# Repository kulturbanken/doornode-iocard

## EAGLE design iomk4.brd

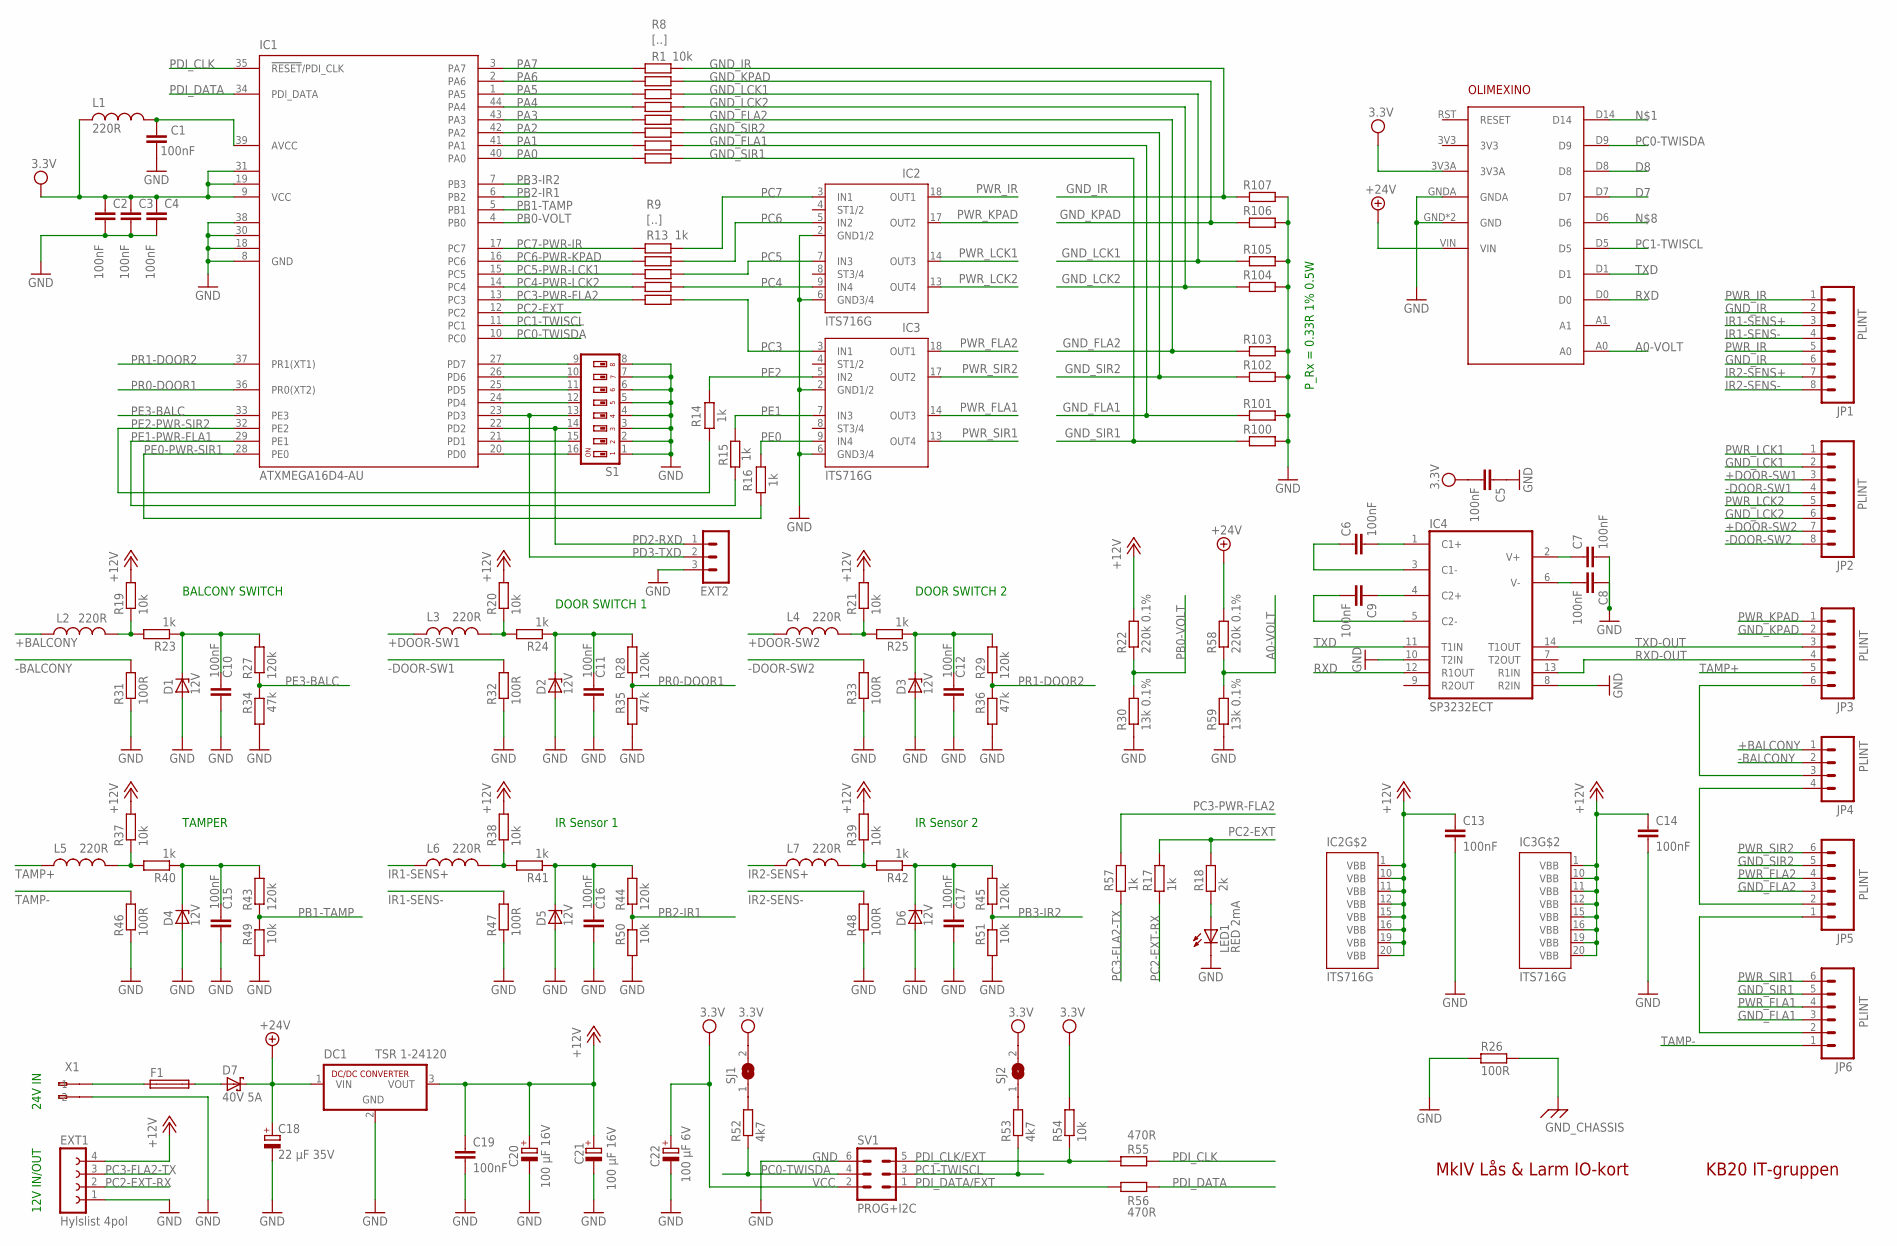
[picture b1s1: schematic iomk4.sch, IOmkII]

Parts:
C1, C2, C3, C4, C5, C6, C7, C8, C9, C10, C11, C12, C13, C14, C15, C16, C17, C19: 100nF; C0805
C18: 22 µF 35V; D/7343-31R
C20, C21: 100 µF 16V; D/7343-31R
C22: 100 µF 6V; CT6032
D1, D2, D3, D4, D5, D6: 12V; SOD80C
D7: 40V 5A; SMB
DC1: TSR 1-24120; SIP3
EXT1: Hylslist 4pol; FE04
EXT2: DEBUG PINS; MA03
F1: Fuse Holder; FTP/60
IC1: ATXMEGA16D4-AU; TQFP44; MPN ATXMEGA16A4-AU
IC2, IC3: ITS716G; PG-DSO-20
IC4: SP3232ECT; SO16L; MPN MAX3232CSE+
JP1, JP2: PLINT; FK-MPT-8-3,5
JP3, JP5, JP6: PLINT; FK-MPT-6-3,5
JP4: PLINT; FK-MPT-4-3.5
L1, L2, L3, L4, L5, L6, L7: 220R; L0805
LED1: RED 2mA; SML0603
OLIMEXINO-STM1: OLIMEXINO; OLIMEXINO-STM32
R1, R2, R3, R4, R5, R6, R7, R8, R19, R20, R21, R37, R38, R39, R49, R50, R51, R54: 10k; R0805
R9, R10, R11, R12, R13, R14, R15, R16, R17, R23, R24, R25, R40, R41, R42, R57: 1k; R0805
R18: 2k; R0805
R22, R58: 220k 0.1%; R0805
R26, R31, R32, R33, R46, R47, R48: 100R; R0805
R27, R28, R29, R43, R44, R45: 120k; R0805
R30, R59: 13k 0.1%; R0805
R34, R35, R36: 47k; R0805
R52, R53: 4k7; R0805
R55, R56: 470R; R0805
R100, R101, R102, R103, R104, R105, R106, R107: 0.33R; R1210
S1: DIP switches; DIL08-SMD-MINI
SJ1, SJ2: Solder jumper; SJ
SV1: PROG+I2C; ML6L
X1: PLINT; 255-402-5

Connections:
+12V: C13.1, C14.1, C19.1, C20.+, C21.+, DC1.3 (VOUT), EXT1.4, IC2.1 (VBB), IC2.10 (VBB), IC2.11 (VBB), IC2.12 (VBB), IC2.15 (VBB), IC2.16 (VBB), IC2.19 (VBB), IC2.20 (VBB), IC3.1 (VBB), IC3.10 (VBB), IC3.11 (VBB), IC3.12 (VBB), IC3.15 (VBB), IC3.16 (VBB), IC3.19 (VBB), IC3.20 (VBB), R19.2, R20.2, R21.2, R22.2, R37.2, R38.2, R39.2
+24V: C18.+, D7.C, DC1.1 (VIN), OLIMEXINO-STM1.VIN, R58.2
+BALCONY: JP4.1, L2.1
+DOOR-SW1: JP2.3, L3.1
+DOOR-SW2: JP2.7, L4.1
-BALCONY: JP4.2, R31.2
-DOOR-SW1: JP2.4, R32.2
-DOOR-SW2: JP2.8, R33.2
A0-VOLT: OLIMEXINO-STM1.A0, R58.1, R59.2
D7: OLIMEXINO-STM1.D7
D8: OLIMEXINO-STM1.D8
GND: C1.2, C2.2, C3.2, C4.2, C5.1, C7.2, C8.1, C10.2, C11.2, C12.2, C13.2, C14.2, C15.2, C16.2, C17.2, C18.-, C19.2, C20.-, C21.-, C22.-, D1.A, D2.A, D3.A, D4.A, D5.A, D6.A, DC1.2 (GND), EXT1.1, EXT2.3, IC1.8 (GND), IC1.18 (GND1), IC1.30 (GND2), IC1.38 (GND3), IC2.2 (GND1/2), IC2.6 (GND3/4), IC3.2 (GND1/2), IC3.6 (GND3/4), IC4.8 (R2IN), IC4.10 (T2IN), IC4.15 (GND), LED1.C, OLIMEXINO-STM1.GND, OLIMEXINO-STM1.GND2 (GND), OLIMEXINO-STM1.GNDA, R26.2, R30.1, R31.1, R32.1, R33.1, R34.2, R35.2, R36.2, R46.1, R47.1, R48.1, R49.2, R50.2, R51.2, R59.1, R100.2, R101.2, R102.2, R103.2, R104.2, R105.2, R106.2, R107.2, S1.1, S1.2, S1.3, S1.4, S1.5, S1.6, S1.7, S1.8, SV1.6, X1.A2 (-2)
GND_CHASSIS: R26.1
GND_FLA1: JP6.3, R2.2, R101.1
GND_FLA2: JP5.3, R4.2, R103.1
GND_IR: JP1.2, JP1.6, R8.2, R107.1
GND_KPAD: JP3.2, R7.2, R106.1
GND_LCK1: JP2.2, R6.2, R105.1
GND_LCK2: JP2.6, R5.2, R104.1
GND_SIR1: JP6.5, R1.2, R100.1
GND_SIR2: JP5.5, R3.2, R102.1
IR1-SENS+: JP1.3, L6.1
IR1-SENS-: JP1.4, R47.2
IR2-SENS+: JP1.7, L7.1
IR2-SENS-: JP1.8, R48.2
unnamed: D7.A, F1.2
unnamed: C1.1, IC1.39 (AVCC), L1.2
unnamed: R53.2, SJ2.1
unnamed: LED1.A, R18.2
unnamed: L3.2, R20.1, R24.2
unnamed: L2.2, R19.1, R23.2
unnamed: C10.1, D1.C, R23.1, R27.2
unnamed: C11.1, D2.C, R24.1, R28.2
unnamed: L4.2, R21.1, R25.2
unnamed: F1.1, X1.A1 (-1)
unnamed: C12.1, D3.C, R25.1, R29.2
unnamed: R52.2, SJ1.1
unnamed: L6.2, R38.1, R41.2
unnamed: JP3.6, JP4.3
unnamed: JP5.1, JP6.2
unnamed: L5.2, R37.1, R40.2
unnamed: JP4.4, JP5.2
unnamed: C15.1, D4.C, R40.1, R43.2
unnamed: C16.1, D5.C, R41.1, R44.2
unnamed: C7.1, IC4.2 (V+)
unnamed: C8.2, IC4.6 (V-)
unnamed: L7.2, R39.1, R42.2
unnamed: C17.1, D6.C, R42.1, R45.2
unnamed: C6.2, IC4.1 (C1+)
unnamed: C9.2, IC4.5 (C2-)
unnamed: C9.1, IC4.4 (C2+)
unnamed: C6.1, IC4.3 (C1-)
PA0: IC1.40 (PA0), R1.1
PA1: IC1.41 (PA1), R2.1
PA2: IC1.42 (PA2), R3.1
PA3: IC1.43 (PA3), R4.1
PA4: IC1.44 (PA4), R5.1
PA5: IC1.1 (PA5), R6.1
PA6: IC1.2 (PA6), R7.1
PA7: IC1.3 (PA7), R8.1
PB0-VOLT: IC1.4 (PB0), R22.1, R30.2
PB1-TAMP: IC1.5 (PB1), R43.1, R49.1
PB2-IR1: IC1.6 (PB2), R44.1, R50.1
PB3-IR2: IC1.7 (PB3), R45.1, R51.1
PC0-TWISDA: IC1.10 (PC0), OLIMEXINO-STM1.D9, R52.1, SV1.4
PC1-TWISCL: IC1.11 (PC1), OLIMEXINO-STM1.D5, R53.1, SV1.3
PC2-EXT: IC1.12 (PC2), R17.1, R18.1
PC2-EXT-RX: EXT1.2, R17.2
PC3: IC3.3 (IN1), R13.1
PC3-FLA2-TX: EXT1.3, R57.1
PC3-PWR-FLA2: IC1.13 (PC3), R13.2, R57.2
PC4: IC2.9 (IN4), R12.1
PC4-PWR-LCK2: IC1.14 (PC4), R12.2
PC5: IC2.7 (IN3), R11.1
PC5-PWR-LCK1: IC1.15 (PC5), R11.2
PC6: IC2.5 (IN2), R10.1
PC6-PWR-KPAD: IC1.16 (PC6), R10.2
PC7: IC2.3 (IN1), R9.1
PC7-PWR-IR: IC1.17 (PC7), R9.2
PD0: IC1.20 (PD0), S1.16
PD1: IC1.21 (PD1), S1.15
PD2-RXD: EXT2.1, IC1.22 (PD2), S1.14
PD3-TXD: EXT2.2, IC1.23 (PD3), S1.13
PD4: IC1.24 (PD4), S1.12
PD5: IC1.25 (PD5), S1.11
PD6: IC1.26 (PD6), S1.10
PD7: IC1.27 (PD7), S1.9
PDI_CLK: IC1.35 (!RESET!/PDI_CLK), R55.1
PDI_CLK/EXT: R54.1, R55.2, SV1.5
PDI_DATA: IC1.34 (PDI_DATA), R56.1
PDI_DATA/EXT: R56.2, SV1.1
PE0: IC3.9 (IN4), R16.1
PE0-PWR-SIR1: IC1.28 (PE0), R16.2
PE1: IC3.7 (IN3), R15.1
PE1-PWR-FLA1: IC1.29 (PE1), R15.2
PE2: IC3.5 (IN2), R14.1
PE2-PWR-SIR2: IC1.32 (PE2), R14.2
PE3-BALC: IC1.33 (PE3), R27.1, R34.1
PR0-DOOR1: IC1.36 (PR0(XT2)), R28.1, R35.1
PR1-DOOR2: IC1.37 (PR1(XT1)), R29.1, R36.1
PWR_FLA1: IC3.14 (OUT3), JP6.4
PWR_FLA2: IC3.18 (OUT1), JP5.4
PWR_IR: IC2.18 (OUT1), JP1.1, JP1.5
PWR_KPAD: IC2.17 (OUT2), JP3.1
PWR_LCK1: IC2.14 (OUT3), JP2.1
PWR_LCK2: IC2.13 (OUT4), JP2.5
PWR_SIR1: IC3.13 (OUT4), JP6.6
PWR_SIR2: IC3.17 (OUT2), JP5.6
RXD: IC4.12 (R1OUT), OLIMEXINO-STM1.D0
RXD-OUT: IC4.13 (R1IN), JP3.4
TAMP+: JP3.5, L5.1
TAMP-: JP6.1, R46.2
TXD: IC4.11 (T1IN), OLIMEXINO-STM1.D1
TXD-OUT: IC4.14 (T1OUT), JP3.3
VCC: C2.1, C3.1, C4.1, C5.2, C22.+, IC1.9 (VCC), IC1.19 (VCC1), IC1.31 (VCC2), IC4.16 (VCC), L1.1, OLIMEXINO-STM1.3V3A, R54.2, SJ1.2, SJ2.2, SV1.2

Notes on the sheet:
P_Rx = 0.33R 1% 0.5W
BALCONY SWITCH
IR Sensor 1
IR Sensor 2
TAMPER
DOOR SWITCH 1
DOOR SWITCH 2
12V IN/OUT
24V IN
KB20 IT-gruppen
MkIV Lås & Larm IO-kort
[..]

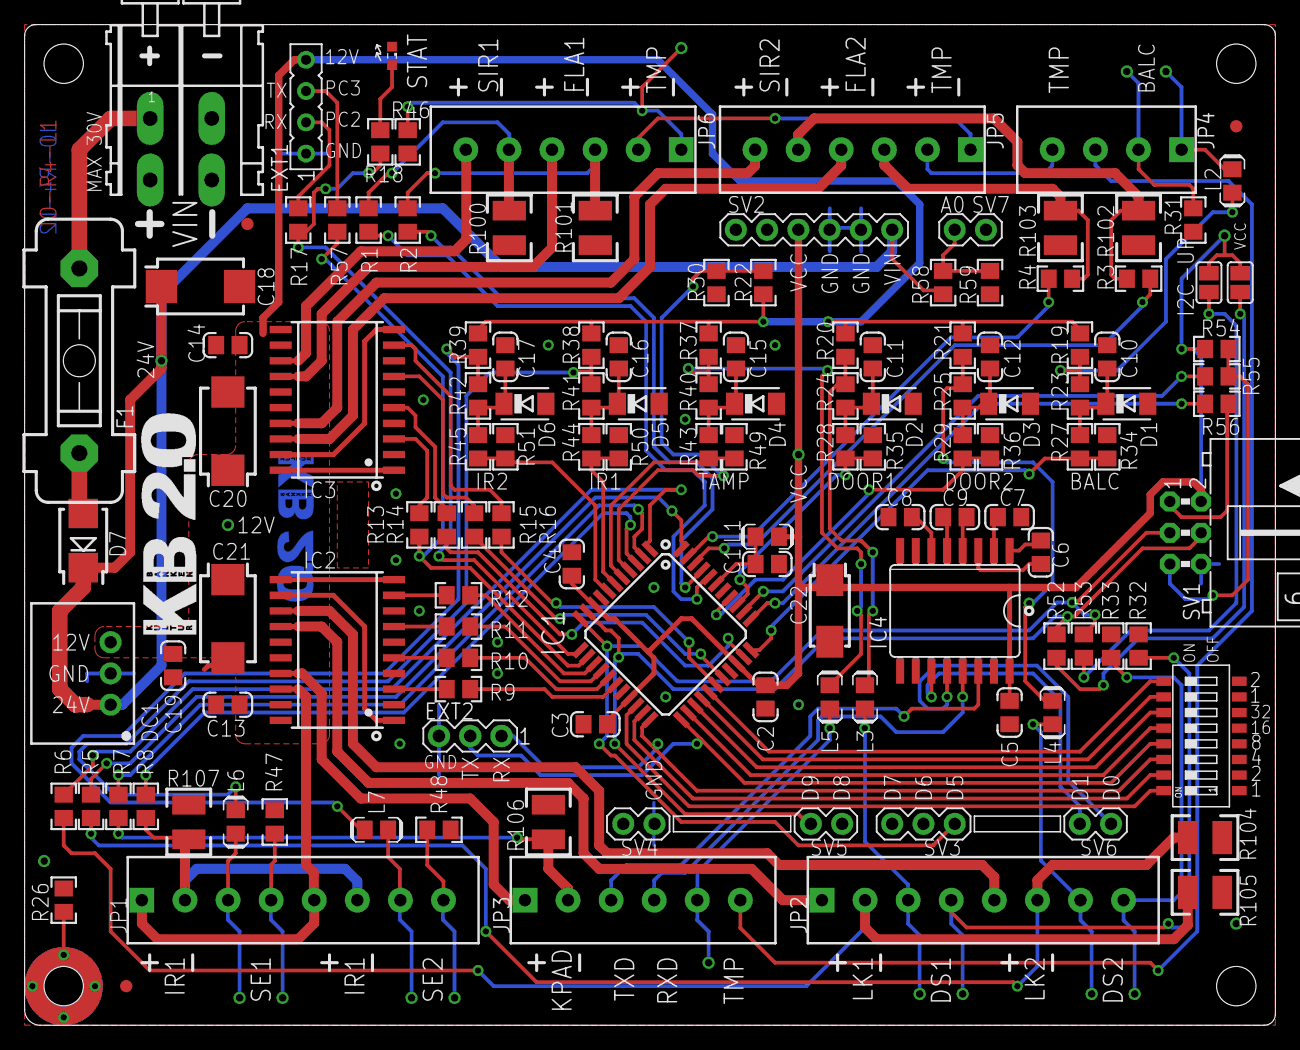
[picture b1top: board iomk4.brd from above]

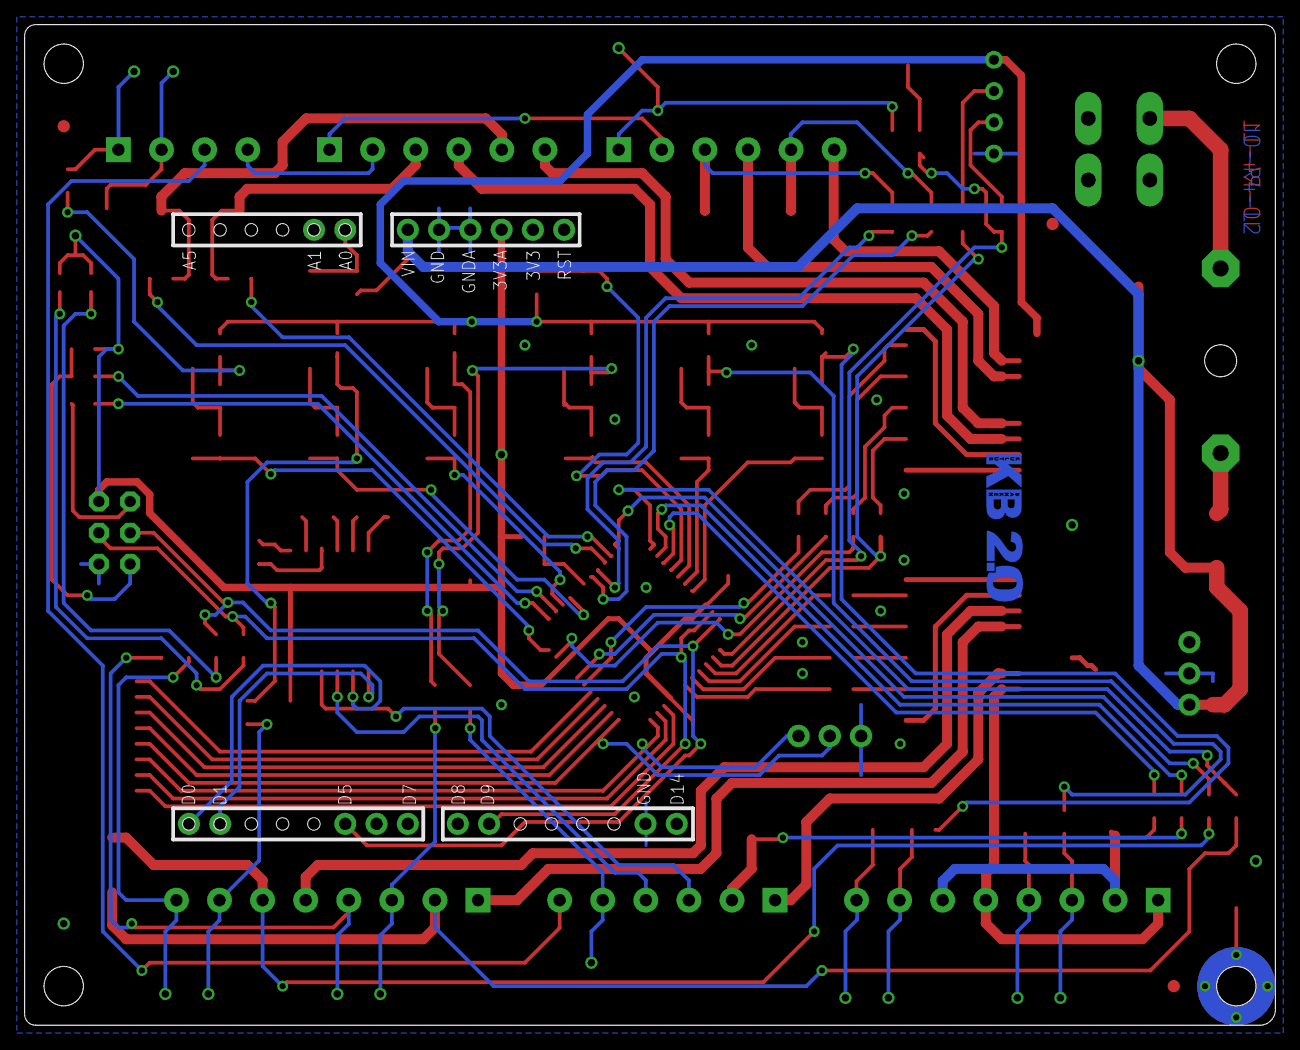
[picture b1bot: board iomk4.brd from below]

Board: 2 copper layers, 101.6 x 81.3 mm, 129 parts (2 on the bottom side), 112 nets.

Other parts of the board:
U$1, U$2, U$3: FIDUCIAL_G10
U$5: KB-LOGG-18MM
U$7: KB-LOGGA-12MM-B

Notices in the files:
parts and their libraries:
dicons: Copyright (C) 2004, Bob Starr (rtzaudio@mindspring.com)
